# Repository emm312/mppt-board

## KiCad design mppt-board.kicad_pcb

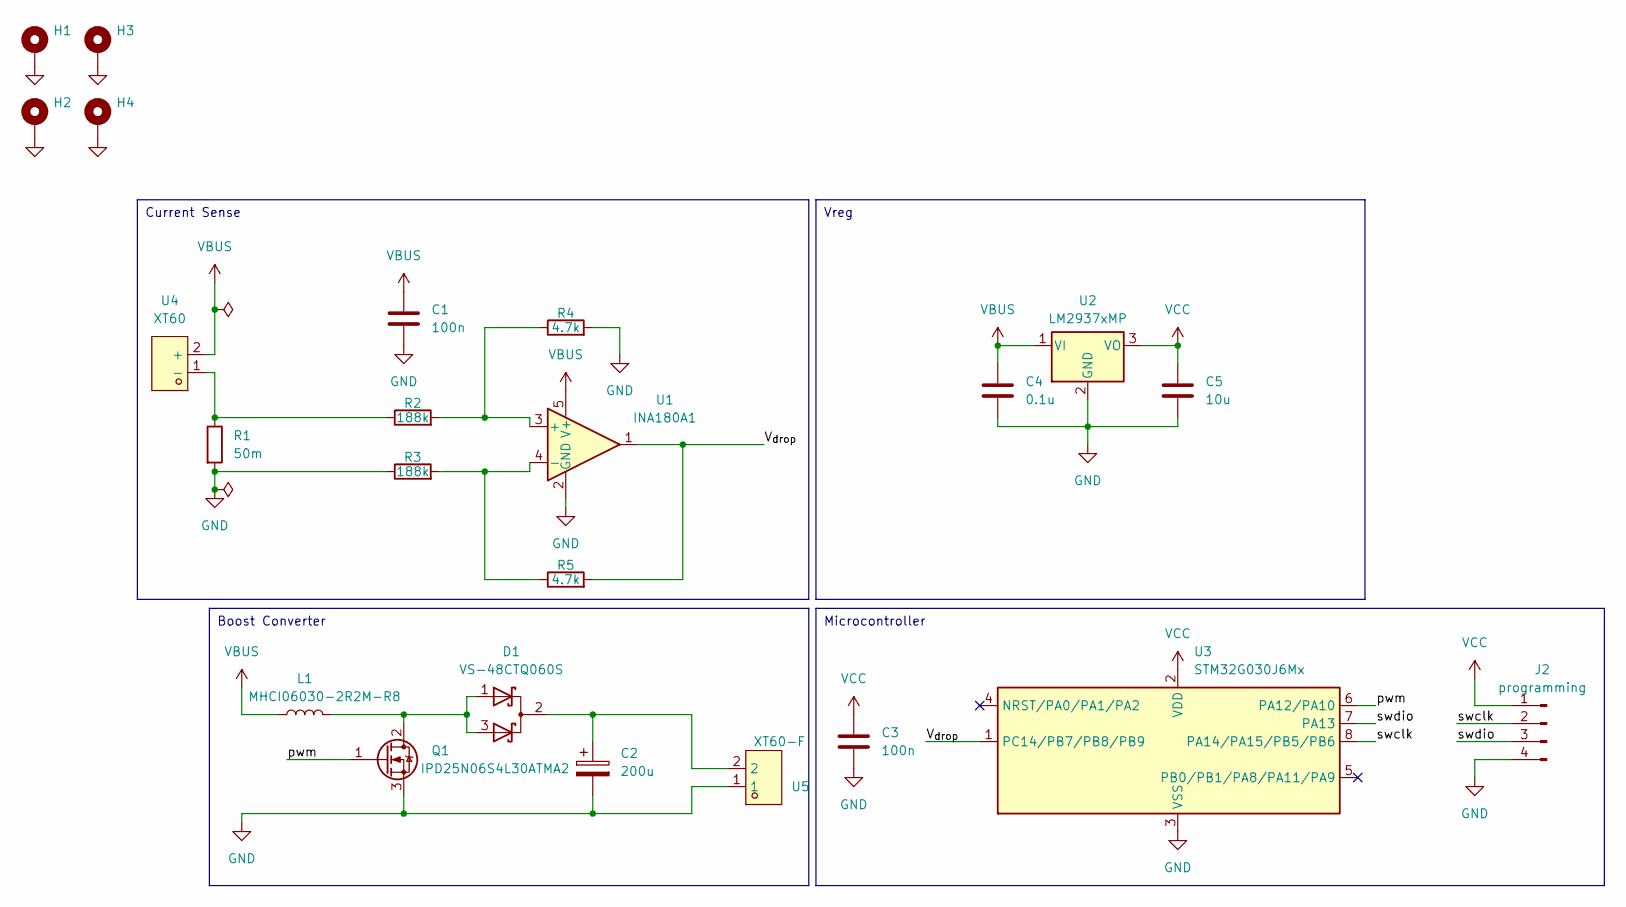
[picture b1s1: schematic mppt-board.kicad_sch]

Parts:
C1, C3: 100n; C_0805_2012Metric
C2: 200u; CP_Radial_D12.5mm_P5.00mm
C4: 0.1u; C_0805_2012Metric
C5: 10u; C_0805_2012Metric
D1: VS-48CTQ060S; TO-263-2
H1, H2, H3, H4: MountingHole_Pad; MountingHole_3.2mm_M3_Pad
J2: programming; PinHeader_1x04_P2.54mm_Vertical
L1: MHCI06030-2R2M-R8; L_Bourns_SRP7028A_7.3x6.6mm
Q1: IPD25N06S4L30ATMA2; TO-252-2
R1: 50m; R_2512_6332Metric
R2, R3: 188k; R_0805_2012Metric
R4, R5: 4.7k; R_0805_2012Metric
U1: INA180A1; SOT-23-5
U2: LM2937xMP; SOT-223-3_TabPin2
U3: STM32G030J6Mx; SOIC-8_3.9x4.9mm_P1.27mm
U4: XT60; CONN-TH_XT60; LCSC Part C98733
U5: XT60-F; CONN-TH_XT60PB-F; LCSC Part C98734

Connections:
/V_{drop}: R5.2, U1.1, U3.1 (PC14/PB7/PB8/PB9)
/pwm: Q1.1 (G), U3.6 (PA12/PA10)
/swclk: J2.2, U3.8 (PA14/PA15/PB5/PB6)
/swdio: J2.3, U3.7 (PA13)
GND: C1.2, C2.2, C3.2, C4.2, C5.2, H1.1, H2.1, H3.1, H4.1, J2.4, Q1.3 (S), R1.2, R3.1, R4.2, U1.2 (GND), U2.2 (GND), U3.3 (VSS), U5.1
unnamed: C2.1, D1.2 (K), U5.2
unnamed: D1.1 (A), D1.3 (A), L1.2, Q1.2 (D)
unnamed: R2.2, R4.1, U1.3 (+)
unnamed: R3.2, R5.1, U1.4 (-)
unnamed: R1.1, R2.1, U4.1 (-)
VBUS: C1.1, C4.1, L1.1, U1.5 (V+), U2.1 (VI), U4.2 (+)
VCC: C3.1, C5.1, J2.1, U2.3 (VO), U3.2 (VDD)

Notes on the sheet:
Current Sense
Boost Converter
Microcontroller
Vreg

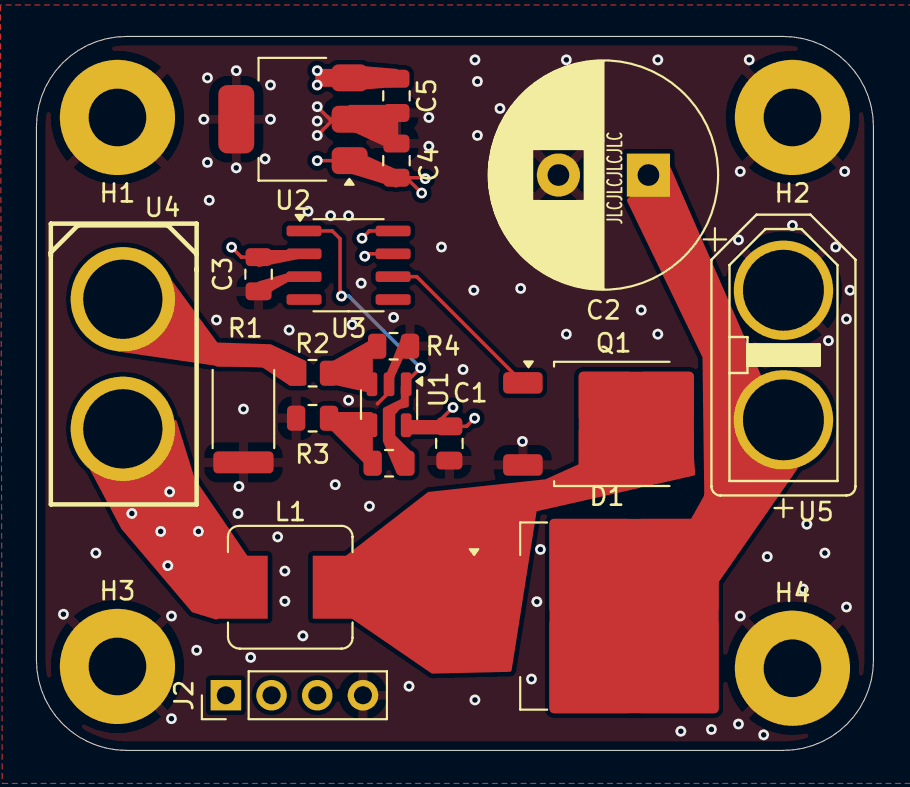
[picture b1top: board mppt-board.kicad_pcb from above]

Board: 4 copper layers, 46.5 x 39.7 mm, 23 parts (0 on the bottom side), 12 nets.

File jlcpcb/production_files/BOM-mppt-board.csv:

Comment,Designator,Footprint,LCSC
MHCI06030-2R2M-R8,L1,L_Bourns_SRP7028A_7.3x6.6mm,C108293
INA180A1,U1,SOT-23-5,C122228
LM2937xMP,U2,SOT-223-3_TabPin2,C140265
4.7k,"R4,R5",R_0805_2012Metric,C17673
188k,"R2,R3",R_0805_2012Metric,C218377
50m,R1,R_2512_6332Metric,C2903475
IPD25N06S4L30ATMA2,Q1,TO-252-2,C3279077
200u,C2,CP_Radial_D12.5mm_P5.00mm,C443147
100n,"C1,C3,C4",C_0805_2012Metric,C49678
VS-48CTQ060S,D1,TO-263-2,C506525
programming,J2,PinHeader_1x04_P2.54mm_Vertical,C6332197
STM32G030J6Mx,U3,SOIC-8_3.9x4.9mm_P1.27mm,C724041
10u,C5,C_0805_2012Metric,C84416
XT60,U4,CONN-TH_XT60,C98733
XT60-F,U5,CONN-TH_XT60PB-F,C98734

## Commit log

2024-09-25 init
2024-09-25 redo
